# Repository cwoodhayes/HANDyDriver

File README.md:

# HANDyDriver: Open-Source Motor Driver Board

HANDyDriver is an open-source BLDC motor driver board designed for versatility and small size, targeted to applications in haptics and dextrous manipulation in robotics. 

It is maintained by the [Center for Robotics and Biosystems at Northwestern University](https://robotics.northwestern.edu/), and supported by the [National Science Foundation HAND ERC](https://hand-erc.org/).

## Contributing & Use
This project is built on [KiCad](https://www.kicad.org/); to modify or use it, install KiCad v9.0 and import `HANDyDriver.kicad_pro` as a project. 

To contribute, please fork the repository and submit a pull request with your changes. For any questions or issues, please open an issue on the GitHub repository.

## Software Library: NU Control
An FOC motor control library targeting the Arduino Teensy v4.0 is maintained alongside this hardware design. See the [NUControl](https://github.com/NU-AIET/NUControl) repo for more information.

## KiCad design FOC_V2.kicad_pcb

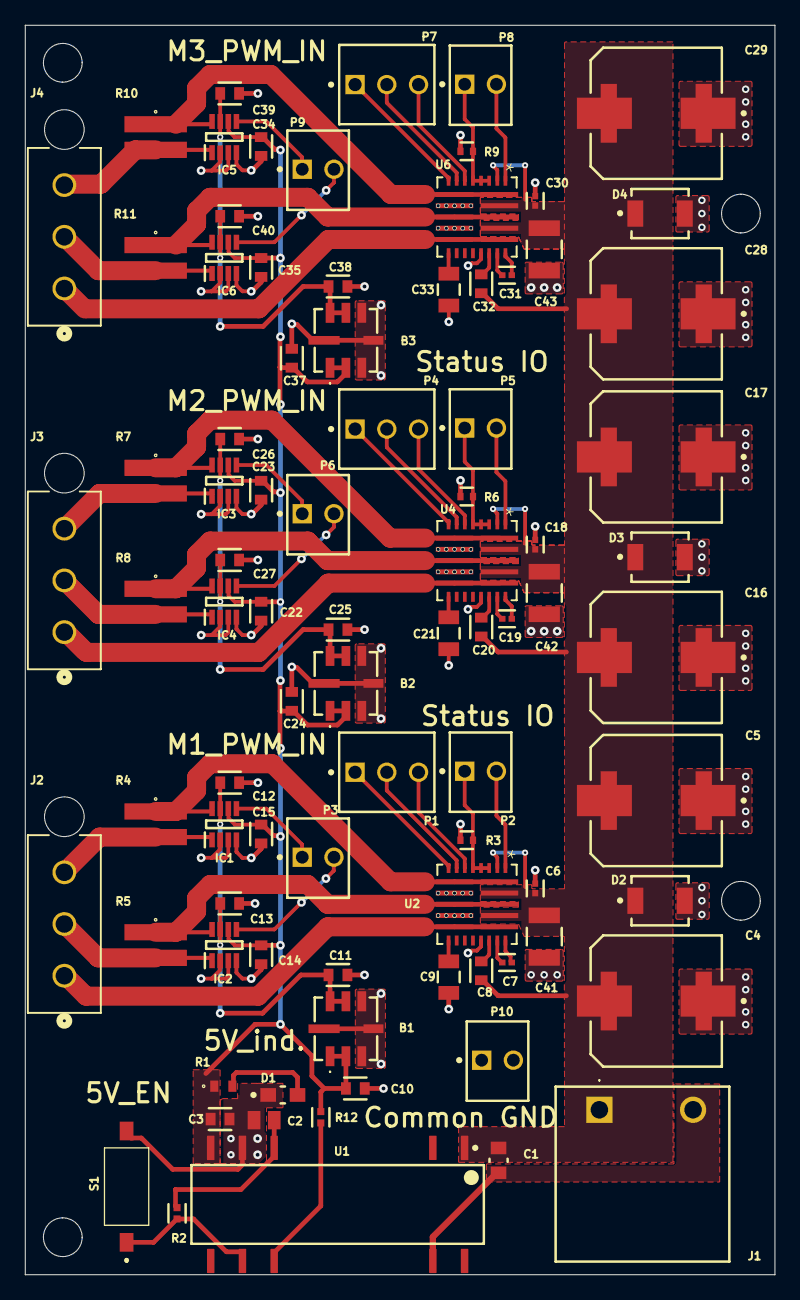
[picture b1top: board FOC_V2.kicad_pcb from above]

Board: 2 copper layers, 60.0 x 100.0 mm, 86 parts (0 on the bottom side), 58 nets.

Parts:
B1: M1_REF; REF7033QFKHT
B2: M2_REF; REF7033QFKHT
B3: M3_REF; REF7033QFKHT
C1: 2.2uF; FP-0805-L_2_01_0_2-W_1_25-MFG
C2: 08053C105J4T2A; CAPC2012X140N
C3, C10, C12, C13, C14, C15, C22, C23, C24, C26, C27, C34, C35, C37, C39, C40: 0.1uF; FP-CL10B104KA8VPJC-MFG
C4, C5, C16, C17, C28, C29: 150uF; FP-EEH-G12-V-MFG
C6, C7, C18, C19, C30, C31: 0.1uF; FP-CL779-IPC_C
C8, C11, C20, C25, C32, C38: 1uF; FP-CL10B105KA8VPJC-MFG
C9, C21, C33: 4.7uF; FP-CL31-IPC_C
C41, C42, C43: 10uF; FP-1210-L_3_2_0_5-W_2_5_0-MFG
D1: 5V_ind.; FP-APT2012LZGCK-MFG
D2, D3, D4: SMBJ24A; FP-SMBJ-MFG
IC1, IC2, IC3, IC4, IC5, IC6: INA241A2IDDFR; SOT65P280X110-8N
J1: 8000078306
J2: Motor1; CON3_1X3_P163_VMNL-1MTG_TYC
J3: Motor2; CON3_1X3_P163_VMNL-1MTG_TYC
J4: Motor3; CON3_1X3_P163_VMNL-1MTG_TYC
P1: M1_PWM_IN; MOLX-22-23-2031_V
P2, P5, P8: Status IO; MOLX-22-23-2021_V
P3, P6, P9: Current Sense Output; MOLX-22-23-2021_V
P4: M2_PWM_IN; MOLX-22-23-2031_V
P7: M3_PWM_IN; MOLX-22-23-2031_V
P10: Common GND; MOLX-22-23-2021_V
R1: ERJ-PA3D1181V; ERJP03_PA3_(0603)
R2, R12: 10kOhms; FP-MCS0402-IPC_B
R3, R6, R9: 4.7kOhms; FP-RT0402-MFG
R4, R5, R7, R8, R10, R11: ERJ-D1DFR010U; ERJD1
S1: 5V_EN; DS04254201BKSMT
U1: DCR022405P-U; DVS0010A_L
U2, U4, U6: MPQ6541GQKTE-AEC1-P; TQFN-26_MPQ6541_MNP

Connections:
5V: B1.1, B1.2, B2.1, B2.2, B3.1, B3.2, C3.1, C10.1, C14.1, C15.1, C22.1, C23.1, C24.1, C34.1, C35.1, C37.1, IC1.6, IC2.6, IC3.6, IC4.6, IC5.6, IC6.6, R1.1, R12.2, U1.9
5V_ERR: R12.1, U1.12
24V: C1.1, C4.2, C5.2, C6.2, C8.2, C16.2, C17.2, C18.2, C20.2, C28.2, C29.2, C30.2, C32.2, C41.2, C42.2, C43.2, D2.1, D3.1, D4.1, J1.1, U1.1, U2.2, U2.23, U2.25, U4.2, U4.23, U4.25, U6.2, U6.23, U6.25
EN1: P2.1, R3.1, U2.3, U2.4, U2.5
EN2: P5.1, R6.1, U4.3, U4.4, U4.5
EN3: P8.1, R9.1, U6.3, U6.4, U6.5
GND: B1.3, B1.4, B1.5, B1.8, B2.3, B2.4, B2.5, B2.8, B3.3, B3.4, B3.5, B3.8, C1.2, C2.2, C3.2, C4.1, C5.1, C6.1, C9.2, C10.2, C11.2, C12.2, C13.2, C14.2, C15.2, C16.1, C17.1, C18.1, C21.2, C22.2, C23.2, C24.2, C25.2, C26.2, C27.2, C28.1, C29.1, C30.1, C33.2, C34.2, C35.2, C37.2, C38.2, C39.2, C40.2, C41.1, C42.1, C43.1, D1.1, D2.2, D3.2, D4.2, IC1.2, IC1.3, IC1.4, IC2.2, IC2.3, IC2.4, IC3.2, IC3.3, IC3.4, IC4.2, IC4.3, IC4.4, IC5.2, IC5.3, IC5.4, IC6.2, IC6.3, IC6.4, J1.2, P10.1, P10.2, R3.2, R6.2, R9.2, S1.2, U1.8, U1.17, U2.10, U2.12, U2.18, U4.10, U4.12, U4.18, U6.10, U6.12, U6.18
M1_3V3_REF: B1.6, B1.7, C11.1, C12.1, C13.1, IC1.7, IC2.7
M1_Status: P2.2, U2.1
M1_U: P1.3, U2.6
M1_U_CS: IC1.5, P3.1
M1_V: P1.2, U2.7
M1_V_CS: IC2.5, P3.2
M1_W: P1.1, U2.8
M2_3V3_REF: B2.6, B2.7, C25.1, C26.1, C27.1, IC3.7, IC4.7
M2_Status: P5.2, U4.1
M2_U: P4.3, U4.6
M2_U_CS: IC3.5, P6.1
M2_V: P4.2, U4.7
M2_V_CS: IC4.5, P6.2
M2_W: P4.1, U4.8
M3_3V3_REF: B3.6, B3.7, C38.1, C39.1, C40.1, IC5.7, IC6.7
M3_Status: P8.2, U6.1
M3_U: P7.3, U6.6
M3_U_CS: IC5.5, P9.1
M3_V: P7.2, U6.7
M3_V_CS: IC6.5, P9.2
M3_W: P7.1, U6.8
NetC2_1: C2.1, R2.2, U1.7
NetC7_1: C7.1, U2.21
NetC7_2: C7.2, U2.20
NetC8_1: C8.1, U2.19
NetC9_1: C9.1, U2.14
NetC19_1: C19.1, U4.21
NetC19_2: C19.2, U4.20
NetC20_1: C20.1, U4.19
NetC21_1: C21.1, U4.14
NetC31_1: C31.1, U6.21
NetC31_2: C31.2, U6.20
NetC32_1: C32.1, U6.19
NetC33_1: C33.1, U6.14
NetD1_2: D1.2, R1.2
NetR2_1: R2.1, S1.1, U1.11
U1: IC1.1, J2.3, R4.2
U1_S: IC1.8, R4.1, U2.9, U2.26
U2: IC3.1, J3.3, R7.2
U2_S: IC3.8, R7.1, U4.9, U4.26
U3: IC5.1, J4.3, R10.2
U3_S: IC5.8, R10.1, U6.9, U6.26
V1: IC2.1, J2.2, R5.2
V1_S: IC2.8, R5.1, U2.11, U2.24
V2: IC4.1, J3.2, R8.2
V2_S: IC4.8, R8.1, U4.11, U4.24
V3: IC6.1, J4.2, R11.2
V3_S: IC6.8, R11.1, U6.11, U6.24
W1: J2.1, U2.13, U2.22
W2: J3.1, U4.13, U4.22
W3: J4.1, U6.13, U6.22

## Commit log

2026-04-15 import v2 from altium
2026-04-15 renamed component library to match
2026-04-15 renamed everything to HANDy
2026-04-15 added a readme
2026-04-15 further readme additions
2026-04-25 manually fixed component labels in schematic
    kicad imported them without their numbers
